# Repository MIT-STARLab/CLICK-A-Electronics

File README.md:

# CLICK-A-Electronics
Electronics for the CLICK-A payload

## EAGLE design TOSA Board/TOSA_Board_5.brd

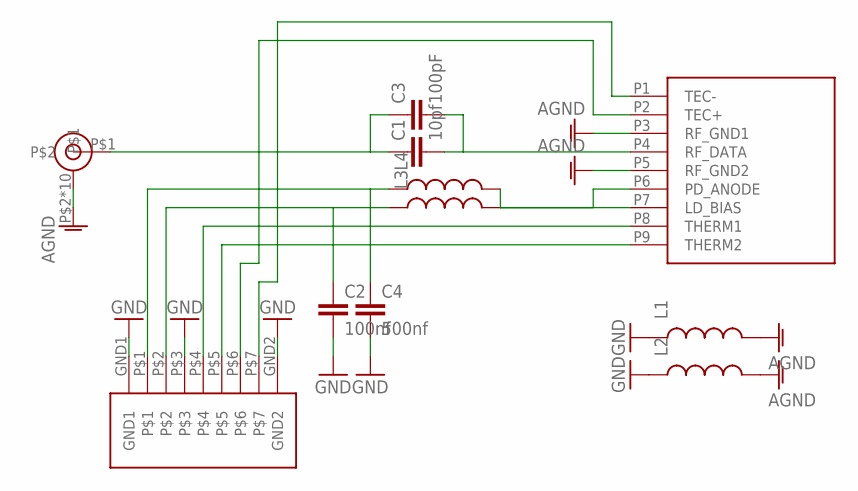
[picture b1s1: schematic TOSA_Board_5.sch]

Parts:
C1: 10pf; C0603K
C2: 100nf; C0603K
C3: 100pF; C0603K
C4: 500nf; C0603K
L1, L2, L3, L4: INDUCTOR30OHM,1.8A; 0603
U$2: TOSA; MSA-9
U$3: EDGE_MOUNT_MMCXMCX; EDGE_MOUNT_MCX
U$4: SAMTEC_T1M_X7; SAMTEX_T1M_X7

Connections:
AGND: L1.2, L2.2, U$2.P3 (RF_GND1), U$2.P5 (RF_GND2), U$3.P$2, U$3.P$3, U$3.P$4, U$3.P$5, U$3.P$6, U$3.P$7, U$3.P$8, U$3.P$9, U$3.P$10, U$3.P$11
GND: C2.2, C4.2, L1.1, L2.1, U$4.GND1, U$4.GND2, U$4.P$3
LD_BIAS: C4.1, L4.1, U$4.P$1
unnamed: C1.1, C3.1, U$3.P$1
unnamed: C1.2, C3.2, U$2.P4 (RF_DATA)
unnamed: L3.2, U$2.P6 (PD_ANODE)
unnamed: L4.2, U$2.P7 (LD_BIAS)
PD_ANODE: C2.1, L3.1, U$4.P$2
TEC+: U$2.P2 (TEC+), U$4.P$6
TEC-: U$2.P1 (TEC-), U$4.P$7
THERM1: U$2.P8 (THERM1), U$4.P$4
THERM2: U$2.P9 (THERM2), U$4.P$5

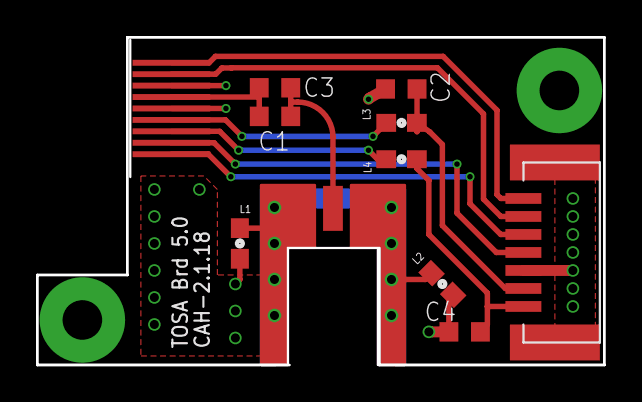
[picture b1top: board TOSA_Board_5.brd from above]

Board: 4 copper layers, 31.5 x 18.2 mm, 11 parts (0 on the bottom side), 12 nets.

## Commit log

2020-10-05 Adding CPU board
2020-10-05 Adding Daughter board
2020-10-05 Adding FPGA board
2020-10-06 Added readme
2020-10-06 Added license, LGPL v3.0
2020-10-06 Adding TOSA and calibration laser boards
2020-10-06 Adding Photodiode board
2020-10-06 Removing history, outjob and html reports

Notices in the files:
parts and their libraries:
SparkFun-Passives: Licensing: Creative Commons ShareAlike 4.0 International - https://creativecommons.org/licenses/by-sa/4.0
